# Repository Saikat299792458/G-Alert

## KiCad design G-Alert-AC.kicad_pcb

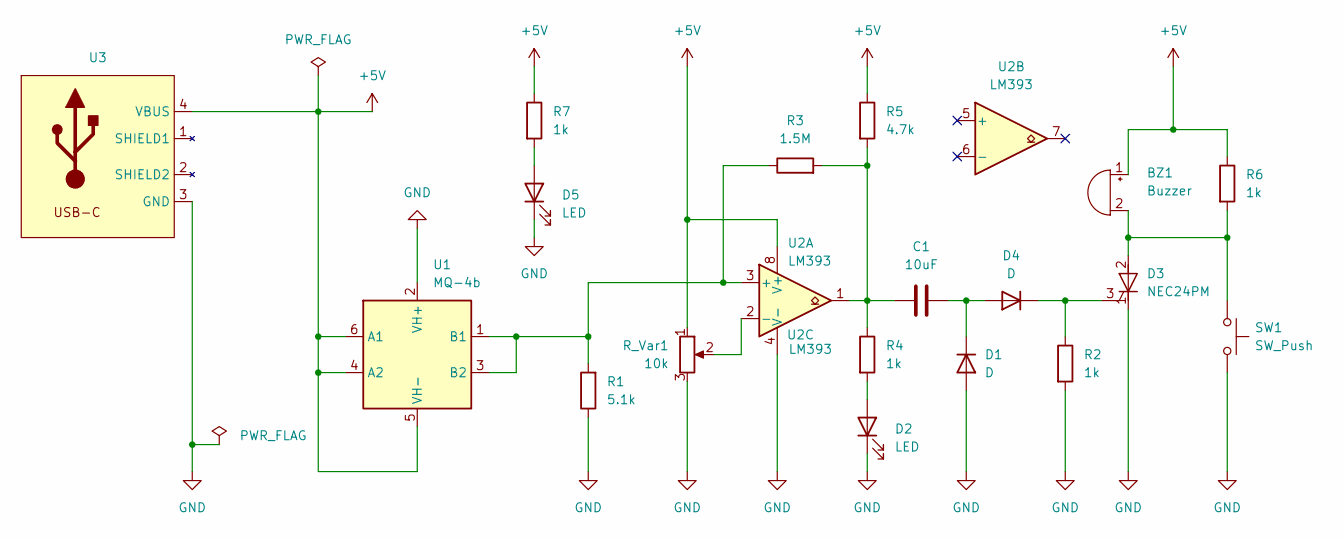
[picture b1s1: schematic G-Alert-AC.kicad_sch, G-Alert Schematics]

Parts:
BZ1: Buzzer; Buzzer_12x9.5RM7.6
C1: 10uF; CP_Radial_D5.0mm_P2.00mm
D1, D4: D; D_DO-35_SOD27_P7.62mm_Horizontal
D2, D5: LED; LED_D5.0mm
D3: NEC24PM; TO-126-3_Vertical
R1: 5.1k; R_Axial_DIN0207_L6.3mm_D2.5mm_P10.16mm_Horizontal
R2, R4, R6, R7: 1k; R_Axial_DIN0207_L6.3mm_D2.5mm_P10.16mm_Horizontal
R3: 1.5M; R_Axial_DIN0207_L6.3mm_D2.5mm_P10.16mm_Horizontal
R5: 4.7k; R_Axial_DIN0207_L6.3mm_D2.5mm_P10.16mm_Horizontal
R_Var1: 10k; Potentiometer_Piher_PT-10-V05_Vertical
SW1: SW_Push; SW_PUSH_6mm
U1: MQ-4b; MQ-6
U2: LM393; DIP-8_W7.62mm
U3: USB-C

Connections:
+5V: BZ1.1 (+), R5.1, R6.1, R7.1, R_Var1.1, U1.4 (A2), U1.5 (VH-), U1.6 (A1), U2.8 (V+), U3.4 (VBUS)
GND: D1.2 (A), D2.1 (K), D3.1 (K), D5.1 (K), R1.1, R2.2, R_Var1.3, SW1.2, U1.2 (VH+), U2.4 (V-), U3.3 (GND)
unnamed: BZ1.2 (-), D3.2 (A), R6.2, SW1.1
unnamed: C1.1, R3.2, R4.1, R5.2, U2.1
unnamed: C1.2, D1.1 (K), D4.2 (A)
unnamed: D2.2 (A), R4.2
unnamed: D3.3 (G), D4.1 (K), R2.1
unnamed: D5.2 (A), R7.2
unnamed: R1.2, R3.1, U1.1 (B1), U1.3 (B2), U2.3 (+)
unnamed: R_Var1.2, U2.2 (-)

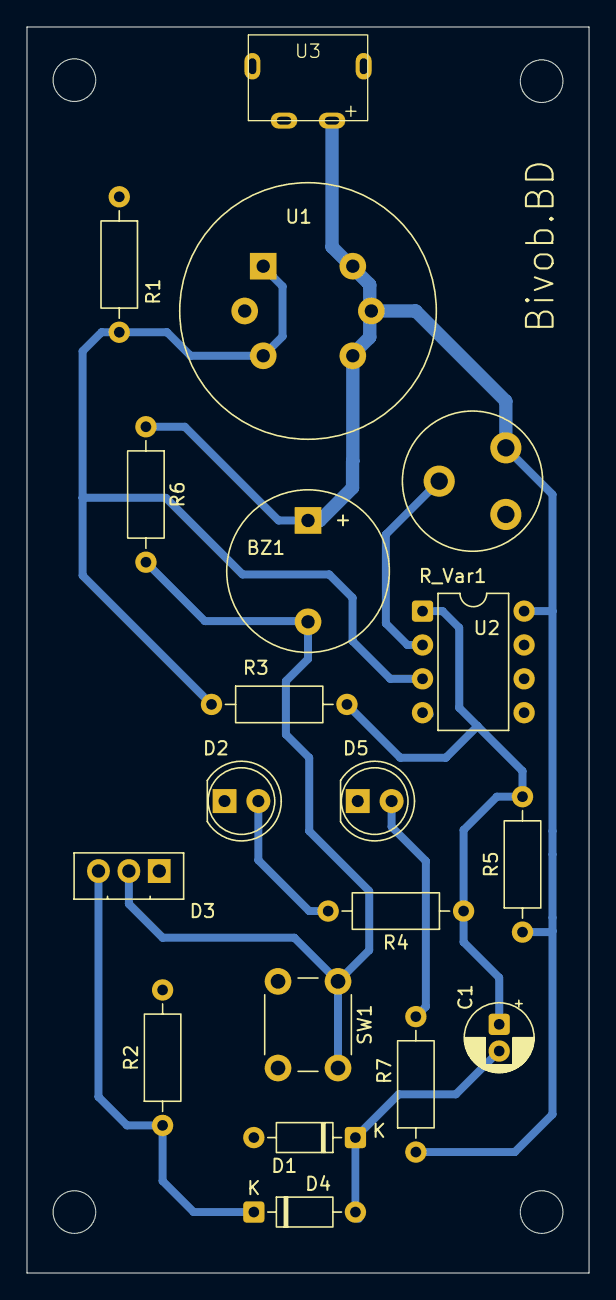
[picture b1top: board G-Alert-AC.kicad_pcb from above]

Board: 2 copper layers, 42.2 x 93.5 mm, 19 parts (0 on the bottom side), 10 nets.

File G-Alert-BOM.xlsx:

Reference | Qty | Value | Vendor | Expected Cost (BDT) | Link | Datasheet
Potentiometer | 3 | 10k | RoboticsBD | 10 | https://store.roboticsbd.com/resistor/1621-potentiometer-10-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
Active Buzzer | 3 | BZ1 | RoboticsBD | 15 | https://store.roboticsbd.com/components/753-active-buzzer-5v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
SCR/Thyristor | 3 | NEC2P4M | RoboticsBD | 40 | https://store.roboticsbd.com/analog-ics-/1450-2p4m-scr-thyri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
Pushbutton | 3 | SW_Push | RoboticsBD | 5 | https://store.roboticsbd.com/electronic-switches/761-push-bu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
Gas Sensor | 3 | MQ-4B | Winsen/RoboticsBD | 185 | https://store.roboticsbd.com/sensors/673-mq-4-methane-natura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 | https://www.winsen-sensor.com/d/files/semiconductor/mq-4b.pdf
Comparator | 3 | LM393 | RoboticsBD | 35 | https://store.roboticsbd.com/analog-ics-/3041-lm393p-dual-di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
USB Connector (B/C) | 3
C1 | 3 | 0.1uF | RoboticsBD | 8
D1 | 3 | 1N4148 | RoboticsBD | 3
D2 | 3 | LED | RoboticsBD | 1
R1 | 3 | 5.1k | RoboticsBD | 1.5 |  | Cumulative Cost
R2,R4,R6 | 9 | 1k | RoboticsBD | 1.5 |  | 1093
R3 | 3 | 1.5M | RoboticsBD | 1.5
R5 | 3 | 4.7k | RoboticsBD | 1.5
Breadboard (Good Quality) | 1 |  | RoboticsBD | 160

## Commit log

2026-05-02 Prototype Update
2026-05-05 Final Update on Schematics
2026-05-06 Footprint Update
2026-05-06 LED Update
2026-05-07 PCB update
2026-05-10 pcb-semifinal
2026-05-10 Panel Update
2026-05-11 Single Side Correction Update
2026-05-12 AC Update with gitignore
2026-05-13 Casing First design
2026-05-14 Design Update 2
